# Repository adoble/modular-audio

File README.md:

# Modular Audio Project - Amplifier Module

An class D amplifier module that can select other digital sources (I2S, S/PDIF).

## System Diagram

### Functional Components

<!-- Removed the ELK renderer as causing problems - see https://github.com/mermaid-js/mermaid-cli/issues/594 -->
<!-- Old code was (first line of the mermaid description): -->
<!-- %%{init: {"flowchart": {"defaultRenderer": "elk"}} }%% -->

```mermaid
flowchart LR

main_ctrl["Main Controller"] -- Parallel Bus --- i2sm[I2S-Multiplexer];
wifi --- antenna1((Antenna <br> 1));

main_ctrl -- I2C --- dsp;
main_ctrl -- SPI+2 --- wifi["WiFi Co-Processor"]
i2sm -- I2S --- dsp["Digital Signal <br> Processor"] -- I2S --- amp[Amplifier];
dsp -- I2S --- toslink_out_converter[TOSLINK<br>Converter] -- "S/PDIF" --- toslink_out{{TOSLINK <br> Out}};

style dsp stroke-dasharray: 5 5;
style toslink_out_converter stroke-dasharray: 5 5;
style toslink_out stroke-dasharray: 5 5;

subgraph sources [Sources-In]
    cd{{CD}};
    dvd{{DVD}};
    tos_link_in{{Toslink In}}
end

subgraph source_sel_display [Source Selection Lights]
    direction LR
    cd_source_selected((CD ))
    dvd_source_selected((DVD))
    bluetooth_source_selected((BT ))
    wlan_source_selected((WLAN))
    dab_source_selected((DAB))
end

antenna2((Antenna <br> 2)) --- airlink;
airlink["Airlink/Bluetooth"] -- I2S --- i2sm
cd -- I2S  --- i2sm;
dvd -- "S/PDIF" --- spdif["S/PDIF Module"] -- I2S --- i2sm;
internet-radio["Internet Radio"] -- I2S --- i2sm

tos_link_in -- "S/PDIF" --- toslink_converter[TOSLINK<br>Converter] -- I2S --- i2sm; 
dab["DAB Radio"] -- I2S --- i2sm

amp --- left{{Left}} --- left_spk((Left <br> Speaker)) 
amp --- right{{Right}} --- right_spk((Right <br> Speaker)) 

dsp -- I2S --- sw-dac[Sub-Woofer DAC] --- sw-line-out{{Sub-Woofer<br>Line-Out}} --- active-sw((Active<br>Sub-Woofer))

vol_proc[Volume <br> Processor];
sel_source[Select <br> Source <br>];

subgraph controls[Controls]
    direction TB
    sel_source_btn((Select <br> Source Button))
    vol_knob((Volume <br> Knob))
end

sel_source --- source_sel_display
vol_knob --- vol_proc -- I2C+1--- main_ctrl;
sel_source_btn --- sel_source -- I2C+1--- main_ctrl;

%%click main_ctrl "https://github.com/adoble/modular-audio/blob/main/README.md#controller"%%
%%click i2sm "https://github.com/adoble/modular-audio/tree/main/hardware/i2s-multiplexer" "Click to see sub-repository"%%
```

### Power

```mermaid
    graph LR;

    net{{240V AV}};
    net ---- Relay;
    Relay --- smps[Switched Mode <br> Power Supply];
    smps ---- pwr_24v{24V};
    smps --- reg_5v[5V Regulator];
    smps --- reg_3v3[3.3V Regulator];
    reg_5v --- pwr_5v{5V};
    reg_3v3 --- pwr_3v3{3.3V};

    Battery --- pwr_on_off(("Power <br> On/Off <br> Switch")) --- Relay; 
```

### Symbols used in the Diagrams

```mermaid
graph LR;

subgraph key[Key]
    transducer((<small>Transducer<small>)) ---  pwr_net{<small>Power<br>Net<small>} --- module[<small>Hardware Module<small>] --- ext{{<small>External<br>Connection<small>}};
end
style key stroke-dasharray: 5 5, fill-opacity: 0;

%% Render links invisible
linkStyle 0 stroke:none
linkStyle 1 stroke:none
linkStyle 2 stroke:none
```

<!--  -->

## Functional Component Descriptions

### Controller

Work in Progress!

The controller has the following tasks:

* Select sources
* Receive input fron the volume control and adjust the volume over the DSP. 
* Receive input from the button banks. These are used to interact with the display. 
* Interface with an (Airlift) Wifi board over an extended SPI interface. This is used to download station lists and also 
to control the internet radio module.

Software is [here](/software/main-controller).

Hardware is [here](/hardware/controller).

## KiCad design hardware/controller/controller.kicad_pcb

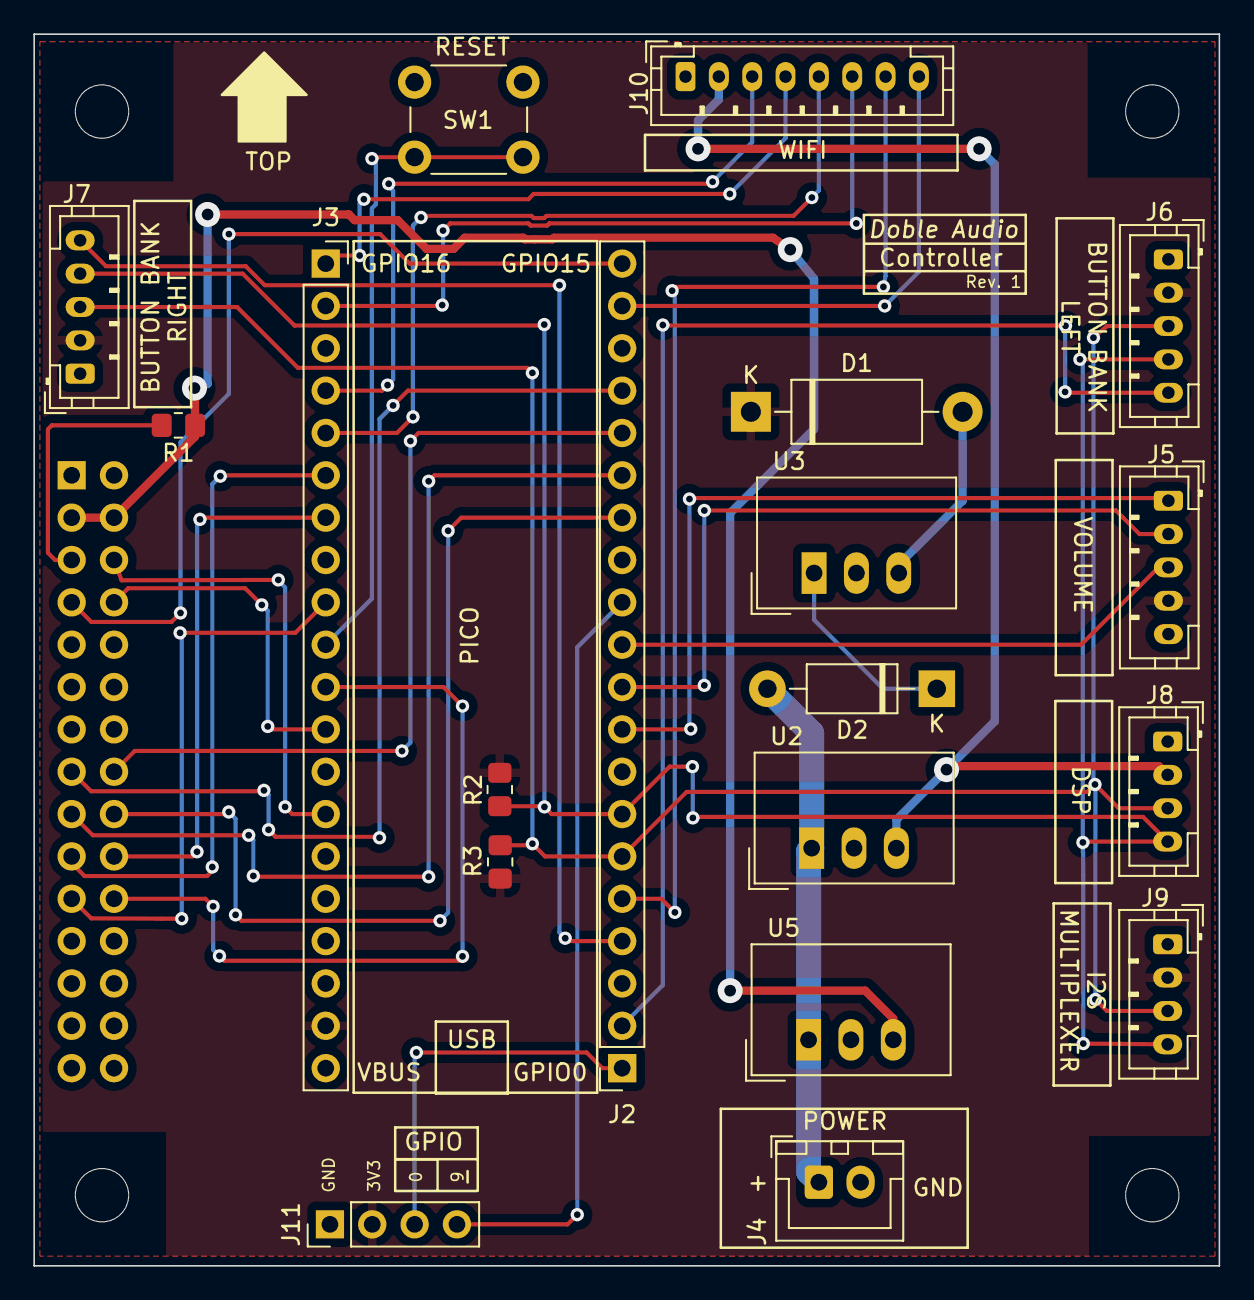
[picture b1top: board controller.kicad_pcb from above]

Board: 2 copper layers, 71.1 x 73.9 mm, 24 parts (1 on the bottom side), 35 nets.

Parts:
D1: D_Schottky; D_DO-15_P12.70mm_Horizontal
D2: 1N4007; D_DO-41_SOD81_P10.16mm_Horizontal
H1, H2, H3, H4: MountingHole; MountingHole_3.2mm_M3
J1: Conn_02x15_Odd_Even; PinSocket_2x15_P2.54mm_Vertical
J2, J3: Conn_01x20; PinSocket_1x20_P2.54mm_Vertical
J4: Conn_01x02; JST_XH_B2B-XH-A_1x02_P2.50mm_Vertical
J5: conn_vol; JST_PH_B5B-PH-K_1x05_P2.00mm_Vertical
J6: conn_bl; JST_PH_B5B-PH-K_1x05_P2.00mm_Vertical
J7: conn_br; JST_PH_B5B-PH-K_1x05_P2.00mm_Vertical
J8: conn_dsp; JST_PH_B4B-PH-K_1x04_P2.00mm_Vertical
J9: conn_i2s_mplx; JST_PH_B4B-PH-K_1x04_P2.00mm_Vertical
J10: conn_wifi; JST_PH_B8B-PH-K_1x08_P2.00mm_Vertical
J11: conn_gpio; PinHeader_1x04_P2.54mm_Vertical
R1: 10k; R_0805_2012Metric_Pad1.20x1.40mm_HandSolder
R2, R3: 2.2K; R_0805_2012Metric_Pad1.20x1.40mm_HandSolder
SW1: RESET; SW_PUSH_6mm_H4.3mm
U2, U3, U5: TSR_1-2433; Converter_DCDC_TRACO_TSR-1_THT

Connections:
+3V3: D1.1 (K), J3.19, J5.4, J6.2, J7.2, J9.2, J11.2, R2.1, R3.1
+3V3_AUX: J8.2, J10.2, U2.3 (Vout)
+3V3_DISPLAY: J1.3, J1.4, R1.1, U5.3 (Vout)
+24V: D2.2 (A), J4.1, U2.1 (Vin), U5.1 (Vin)
/DI.DATA0: J1.15, J2.17
/DI.DATA1: J1.16, J2.16
/DI.DATA2: J1.17, J2.15
/DI.DATA3: J1.18, J2.14
/DI.DATA4: J1.19, J3.6
/DI.DATA5: J1.20, J3.7
/DI.DATA6: J1.21, J3.9
/DI.DATA7: J1.22, J3.11
/DI.LCD_DCX: J1.8, J3.12
/DI.~LCD_WR: J1.6, J3.14
/GPIO0: J2.1, J11.3
/GPIO9: J2.12, J11.4
/I2C0_SCL: J2.7, J6.4, J7.4, J8.4, J9.4, R2.2
/I2C0_SDA: J2.6, J6.3, J7.3, J8.3, J9.3, R3.2
/INT_BL: J2.2, J6.5
/INT_BR: J2.4, J7.5
/LCD_READ: J1.5, R1.2
/MCU_RESET: J3.10, SW1.2
/SPI0_CS: J3.2, J10.6
/SPI0_RX: J3.1, J10.4
/SPI0_SCK: J3.4, J10.3
/SPI0_TX: J3.5, J10.5
/VOL_A: J2.9, J5.1
/VOL_B: J2.10, J5.2
/VOL_C: J2.11, J5.3
/WIFI_BUSY: J2.5, J10.7
/~LCD_CS: J1.7, J2.20
/~WIFI_RESET: J2.19, J10.8
GND: J1.1, J1.2, J1.13, J2.3, J2.8, J2.13, J2.18, J3.3, J3.8, J3.18, J4.2, J5.5, J6.1, J7.1, J8.1, J9.1, J10.1, J11.1, SW1.1, U2.2 (GND), U3.2 (GND), U5.2 (GND)
unnamed: D1.2 (A), U3.3 (Vout)
unnamed: D2.1 (K), U3.1 (Vin)

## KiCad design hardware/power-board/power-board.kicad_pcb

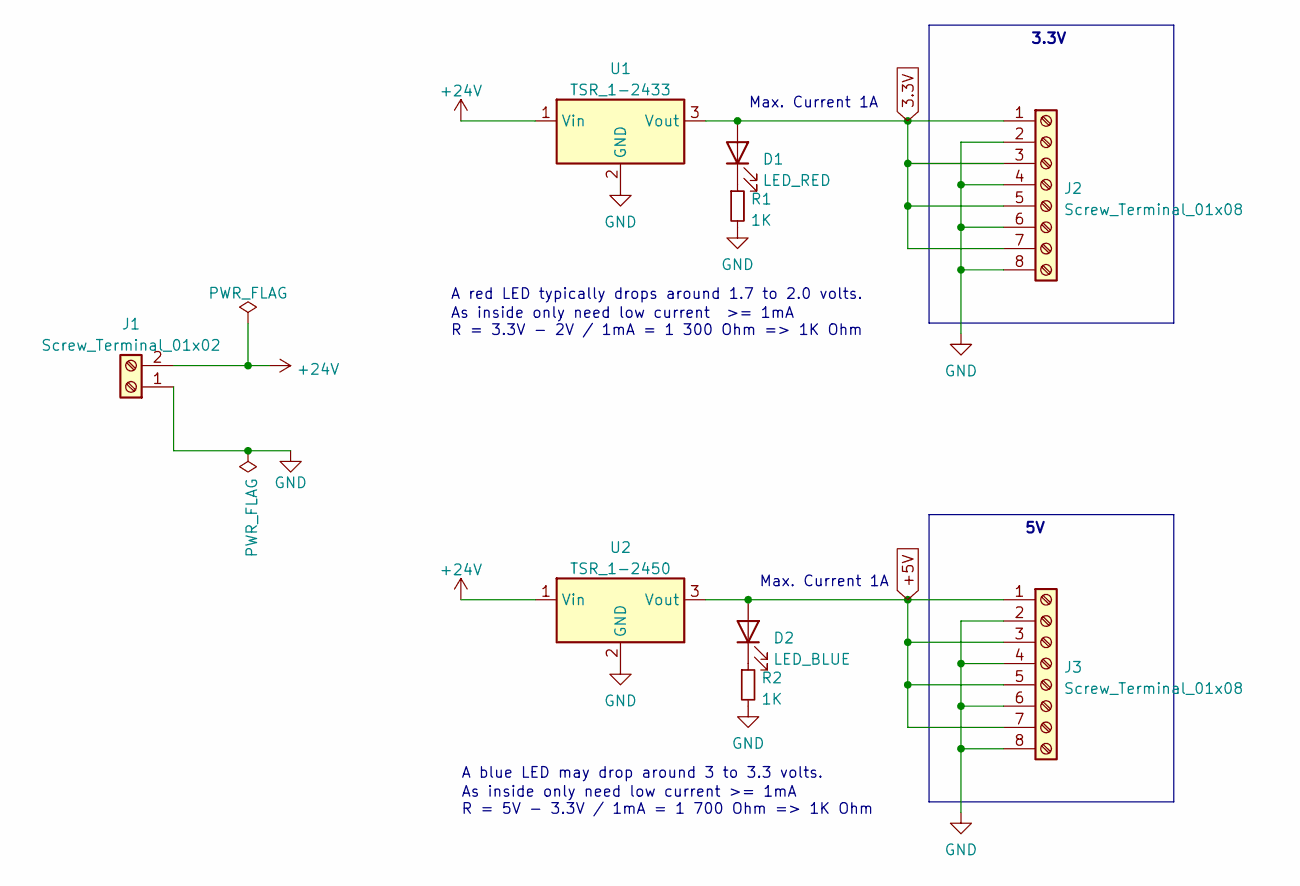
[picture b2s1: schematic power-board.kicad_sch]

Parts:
D1: LED_RED; LED_0805_2012Metric_Pad1.15x1.40mm_HandSolder
D2: LED_BLUE; LED_0805_2012Metric_Pad1.15x1.40mm_HandSolder
J1: Screw_Terminal_01x02; TerminalBlock_bornier-2_P5.08mm
J2, J3: Screw_Terminal_01x08; TerminalBlock_Phoenix_MKDS-3-8-5.08_1x08_P5.08mm_Horizontal
R1, R2: 1K; R_0805_2012Metric_Pad1.20x1.40mm_HandSolder
U1: TSR_1-2433; Converter_DCDC_TRACO_TSR-1_THT
U2: TSR_1-2450; Converter_DCDC_TRACO_TSR-1_THT

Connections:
3.3V: D1.2 (A), J2.1, J2.3, J2.5, J2.7, U1.3 (Vout)
+5V: D2.2 (A), J3.1, J3.3, J3.5, J3.7, U2.3 (Vout)
+24V: J1.2, U1.1 (Vin), U2.1 (Vin)
GND: J1.1, J2.2, J2.4, J2.6, J2.8, J3.2, J3.4, J3.6, J3.8, R1.2, R2.2, U1.2 (GND), U2.2 (GND)
unnamed: D1.1 (K), R1.1
unnamed: D2.1 (K), R2.1

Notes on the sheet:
Max. Current 1A
As inside only need low current >= 1mA R = 3.3V - 2V / 1mA = 1 300 Ohm => 1K Ohm
A red LED typically drops around 1.7 to 2.0 volts.
3.3V
As inside only need low current >= 1mA R = 5V - 3.3V / 1mA = 1 700 Ohm => 1K Ohm
A blue LED may drop around 3 to 3.3 volts.

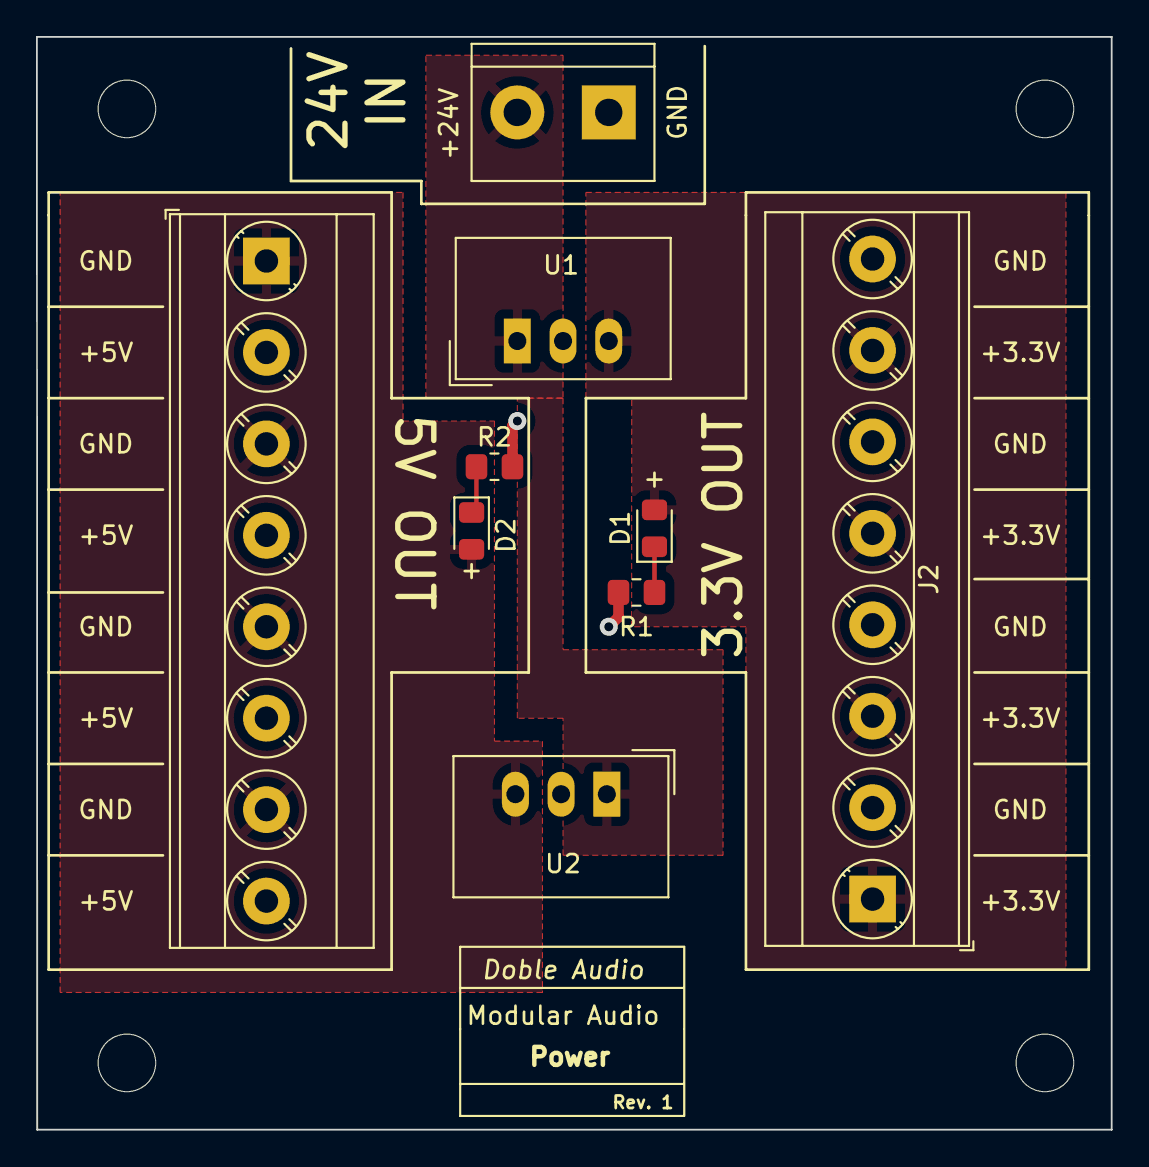
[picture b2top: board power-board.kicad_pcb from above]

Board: 2 copper layers, 59.7 x 60.7 mm, 9 parts (0 on the bottom side), 6 nets.

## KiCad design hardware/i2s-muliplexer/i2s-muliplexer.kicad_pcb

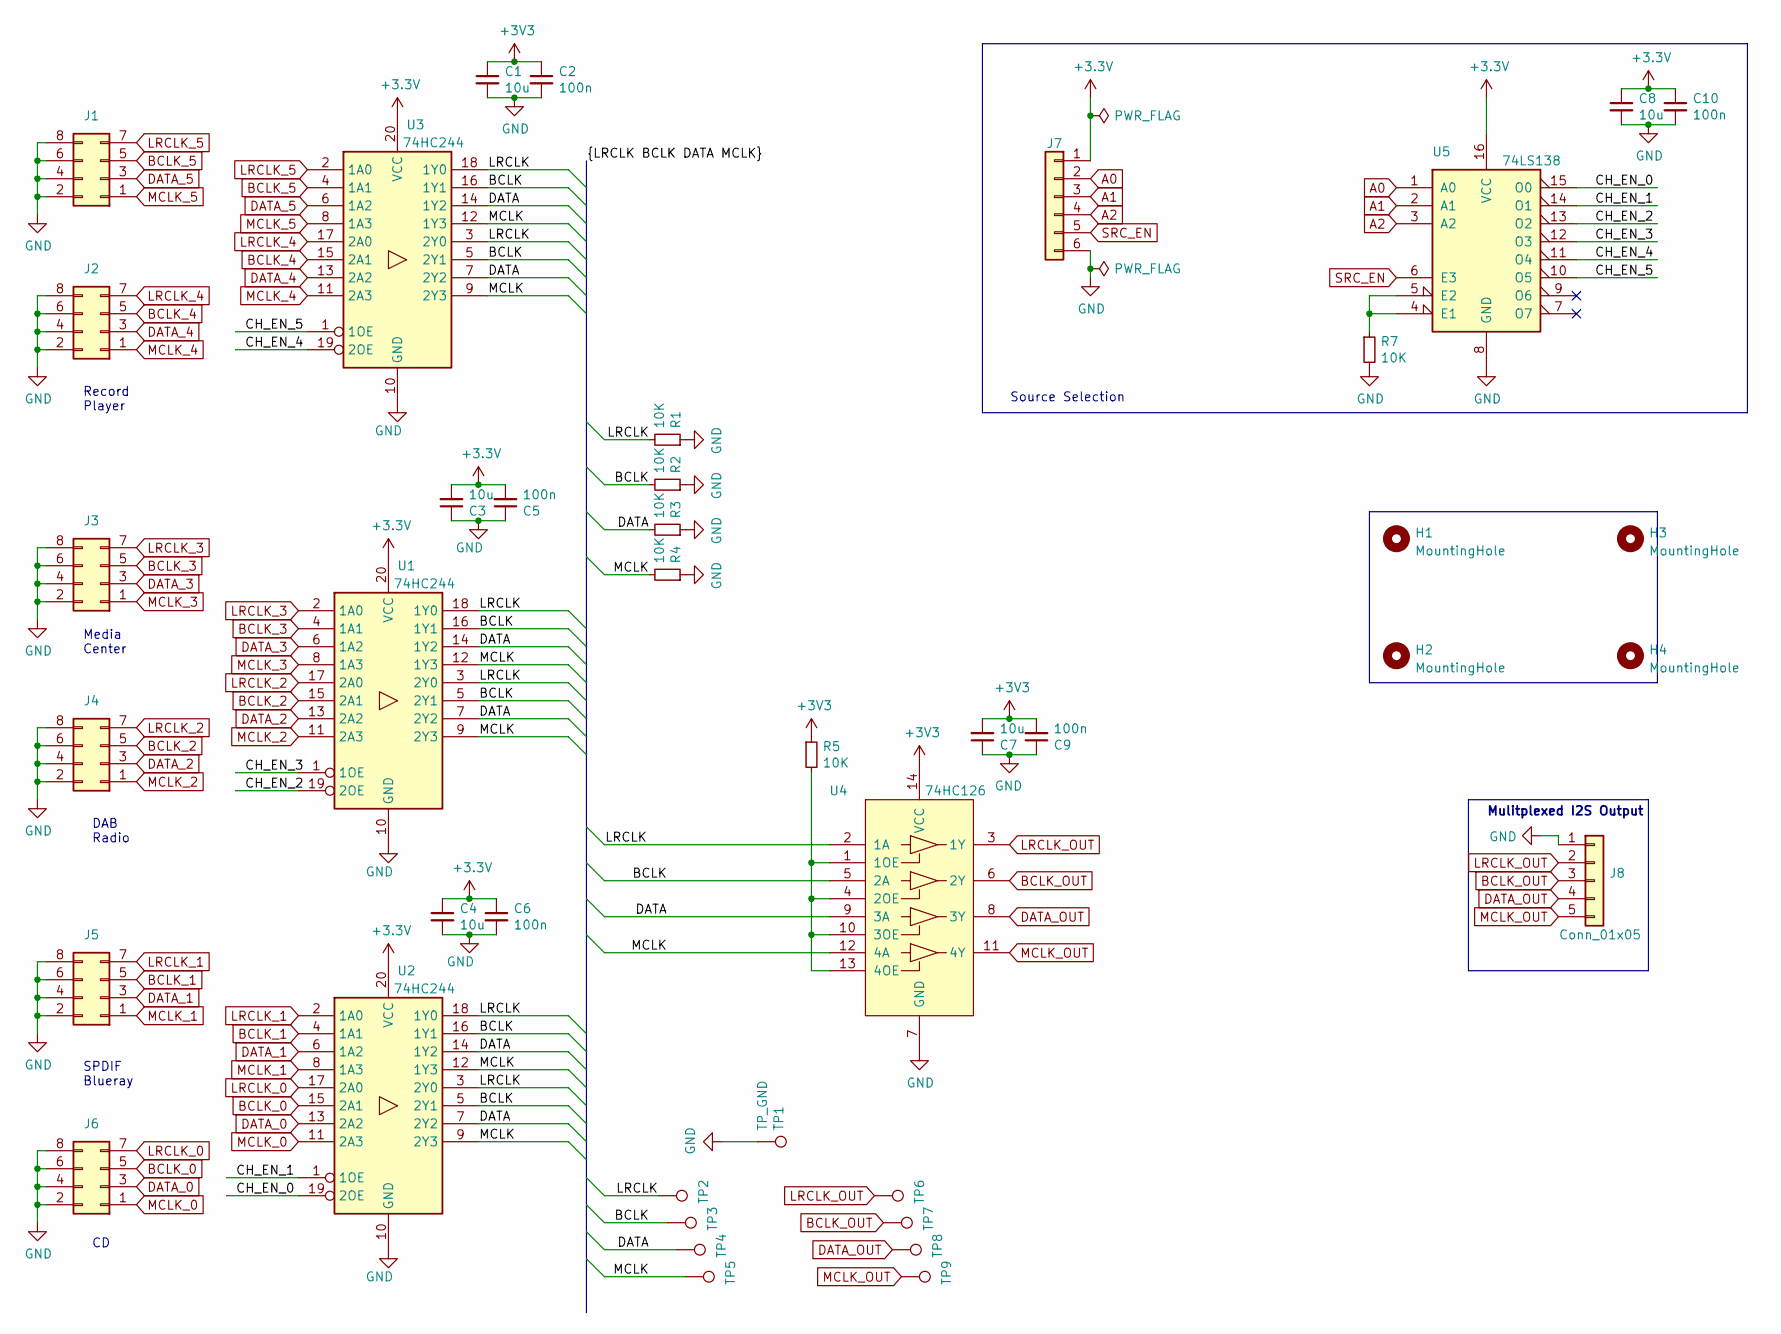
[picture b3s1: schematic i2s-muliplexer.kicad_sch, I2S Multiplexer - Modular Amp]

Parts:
C1, C3, C4, C7, C8: 10u; C_0805_2012Metric_Pad1.15x1.40mm_HandSolder
C2, C5, C6, C9, C10: 100n; C_0805_2012Metric_Pad1.15x1.40mm_HandSolder
H1, H2, H3, H4: MountingHole; MountingHole_3.2mm_M3_DIN965
J1, J2, J3, J4, J5, J6: Conn_02x04_Odd_Even; PinHeader_2x04_P2.54mm_Vertical
J7: Conn_01x06; PinHeader_1x06_P2.54mm_Vertical
J8: Conn_01x05; PinHeader_1x05_P2.54mm_Vertical
R1, R2, R3, R4, R5, R7: 10K; R_0805_2012Metric_Pad1.15x1.40mm_HandSolder
TP1: TP_GND; PinHeader_1x01_P2.54mm_Vertical
TP2, TP3, TP4, TP5, TP6, TP7, TP8, TP9: TestPoint; TestPoint_Pad_2.0x2.0mm
U1, U2, U3: 74HC244; SOIC-20W_7.5x12.8mm_P1.27mm
U4: 74HC126; SOIC-14_3.9x8.7mm_P1.27mm
U5: 74LS138; SOIC-16_3.9x9.9mm_P1.27mm

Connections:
/BCLK: R2.2, TP3.1, U1.5 (2Y1), U1.16 (1Y1), U2.5 (2Y1), U2.16 (1Y1), U3.5 (2Y1), U3.16 (1Y1), U4.5 (2A)
/CH_EN_0: U2.19 (2OE), U5.15 (O0)
/CH_EN_1: U2.1 (1OE), U5.14 (O1)
/CH_EN_2: U1.19 (2OE), U5.13 (O2)
/CH_EN_3: U1.1 (1OE), U5.12 (O3)
/CH_EN_4: U3.19 (2OE), U5.11 (O4)
/CH_EN_5: U3.1 (1OE), U5.10 (O5)
/DATA: R3.2, TP4.1, U1.7 (2Y2), U1.14 (1Y2), U2.7 (2Y2), U2.14 (1Y2), U3.7 (2Y2), U3.14 (1Y2), U4.9 (3A)
/LRCLK: R1.2, TP2.1, U1.3 (2Y0), U1.18 (1Y0), U2.3 (2Y0), U2.18 (1Y0), U3.3 (2Y0), U3.18 (1Y0), U4.2 (1A)
/MCLK: R4.2, TP5.1, U1.9 (2Y3), U1.12 (1Y3), U2.9 (2Y3), U2.12 (1Y3), U3.9 (2Y3), U3.12 (1Y3), U4.12 (4A)
A0: J7.2, U5.1 (A0)
A1: J7.3, U5.2 (A1)
A2: J7.4, U5.3 (A2)
BCLK_0: J6.5, U2.15 (2A1)
BCLK_1: J5.5, U2.4 (1A1)
BCLK_2: J4.5, U1.15 (2A1)
BCLK_3: J3.5, U1.4 (1A1)
BCLK_4: J2.5, U3.15 (2A1)
BCLK_5: J1.5, U3.4 (1A1)
BCLK_OUT: J8.3, TP7.1, U4.6 (2Y)
DATA_0: J6.3, U2.13 (2A2)
DATA_1: J5.3, U2.6 (1A2)
DATA_2: J4.3, U1.13 (2A2)
DATA_3: J3.3, U1.6 (1A2)
DATA_4: J2.3, U3.13 (2A2)
DATA_5: J1.3, U3.6 (1A2)
DATA_OUT: J8.4, TP8.1, U4.8 (3Y)
GND: C1.2, C2.2, C3.1, C4.2, C5.1, C6.2, C7.1, C8.2, C9.1, C10.2, J1.2, J1.4, J1.6, J1.8, J2.2, J2.4, J2.6, J2.8, J3.2, J3.4, J3.6, J3.8, J4.2, J4.4, J4.6, J4.8, J5.2, J5.4, J5.6, J5.8, J6.2, J6.4, J6.6, J6.8, J7.6, J8.1, R1.1, R2.1, R3.1, R4.1, R7.2, TP1.1, U1.10 (GND), U2.10 (GND), U3.10 (GND), U4.7 (GND), U5.8 (GND); also elsewhere on the board
LRCLK_0: J6.7, U2.17 (2A0)
LRCLK_1: J5.7, U2.2 (1A0)
LRCLK_2: J4.7, U1.17 (2A0)
LRCLK_3: J3.7, U1.2 (1A0)
LRCLK_4: J2.7, U3.17 (2A0)
LRCLK_5: J1.7, U3.2 (1A0)
LRCLK_OUT: J8.2, TP6.1, U4.3 (1Y)
MCLK_0: J6.1, U2.11 (2A3)
MCLK_1: J5.1, U2.8 (1A3)
MCLK_2: J4.1, U1.11 (2A3)
MCLK_3: J3.1, U1.8 (1A3)
MCLK_4: J2.1, U3.11 (2A3)
MCLK_5: J1.1, U3.8 (1A3)
MCLK_OUT: J8.5, TP9.1, U4.11 (4Y)
unnamed: R5.2, U4.1 (1OE), U4.4 (2OE), U4.10 (3OE), U4.13 (4OE)
unnamed: R7.1, U5.4 (E1), U5.5 (E2)
SRC_EN: J7.5, U5.6 (E3)

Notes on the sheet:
Mulitplexed I2S Output
Media Center
Source Selection
SPDIF Blueray
Record Player
DAB Radio

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
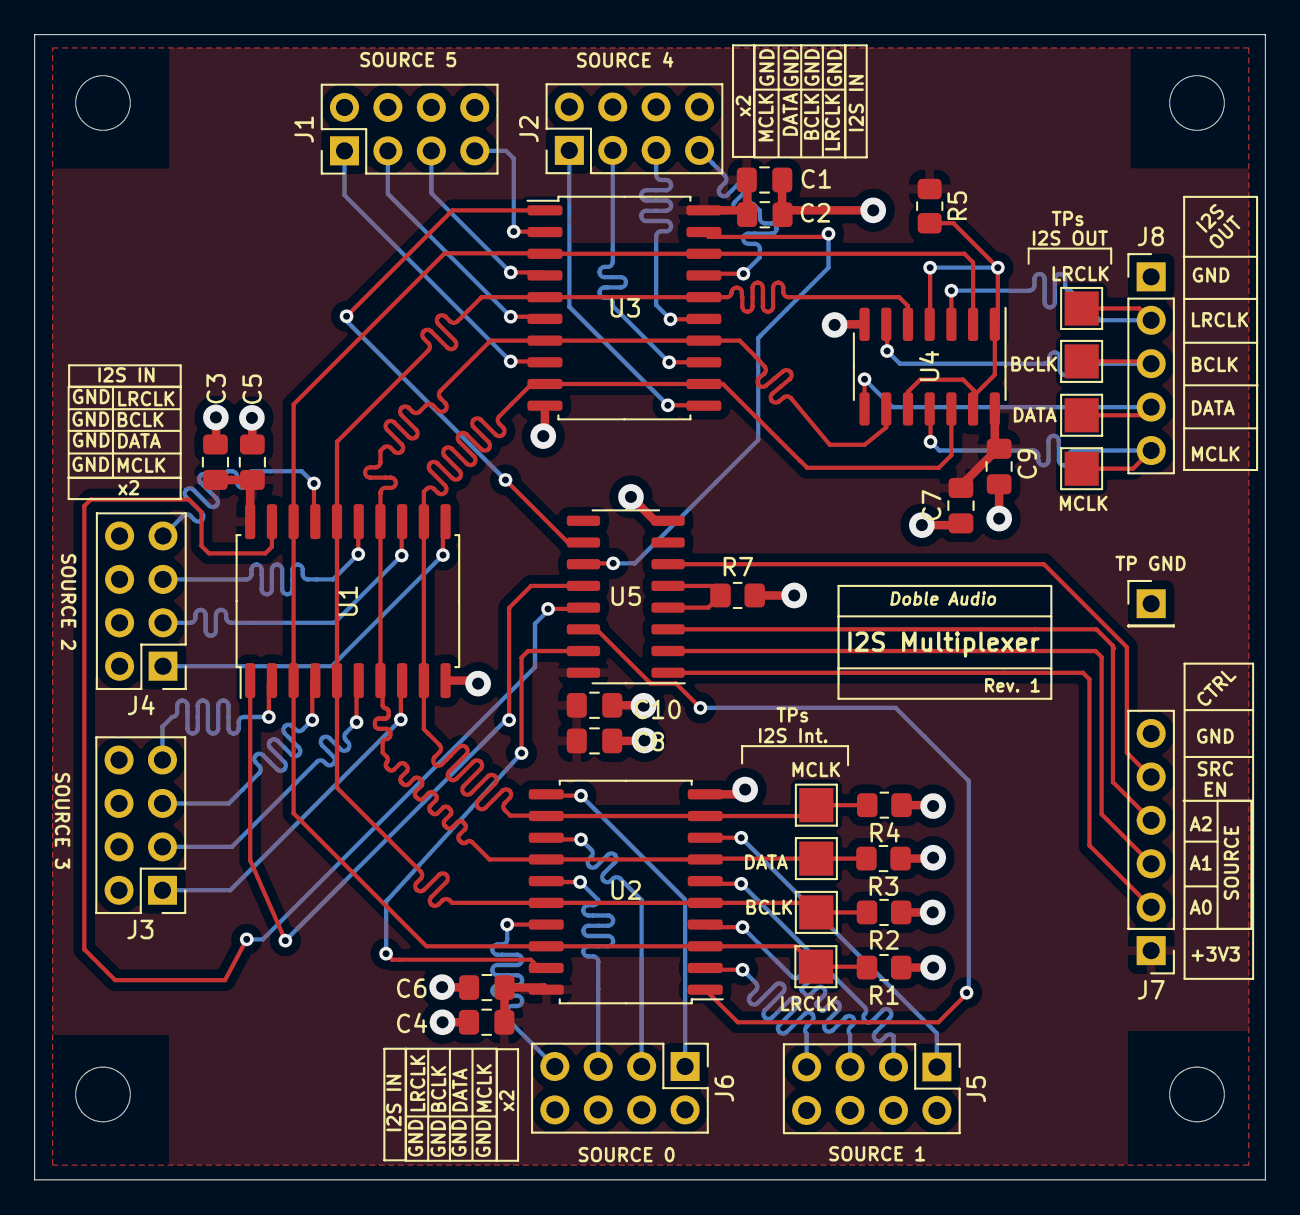
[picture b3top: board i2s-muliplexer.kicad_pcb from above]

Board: 2 copper layers, 72.0 x 67.0 mm, 42 parts (0 on the bottom side), 46 nets.

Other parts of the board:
TP GND: TP_GND; PinHeader_1x01_P2.54mm_Vertical

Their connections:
GND: TP GND.1; also elsewhere on the board

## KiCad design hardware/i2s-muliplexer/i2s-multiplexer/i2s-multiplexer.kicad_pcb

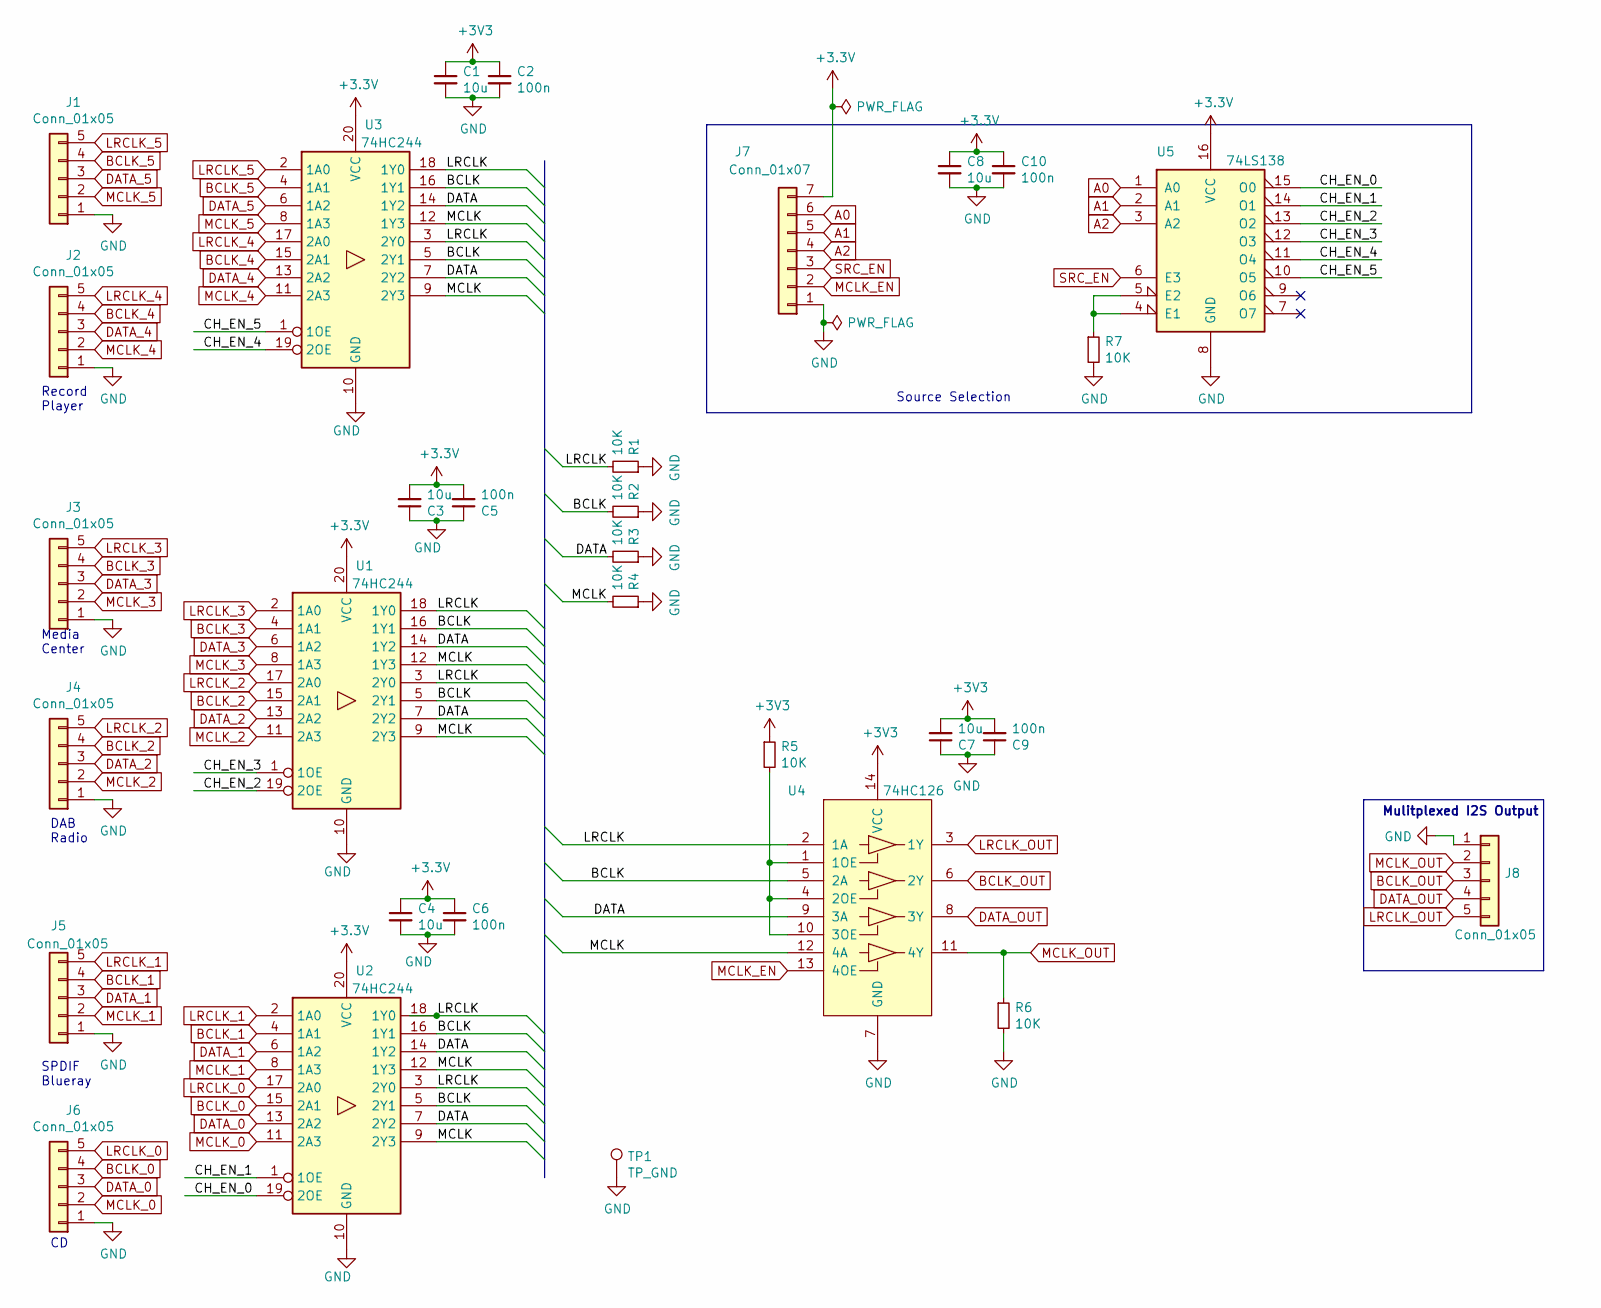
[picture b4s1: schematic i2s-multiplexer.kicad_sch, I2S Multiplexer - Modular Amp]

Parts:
C1, C3, C4, C7, C8: 10u; C_0805_2012Metric_Pad1.15x1.40mm_HandSolder
C2, C5, C6, C9, C10: 100n; C_0805_2012Metric_Pad1.15x1.40mm_HandSolder
J1, J2, J3, J4, J5, J6, J8: Conn_01x05; PinHeader_1x05_P2.54mm_Vertical
J7: Conn_01x07; PinHeader_1x07_P2.54mm_Vertical
R1, R2, R3, R4, R5, R6, R7: 10K; R_0805_2012Metric_Pad1.15x1.40mm_HandSolder
TP1: TP_GND; PinHeader_1x01_P2.54mm_Vertical
U1, U2, U3: 74HC244; SOIC-20W_7.5x12.8mm_P1.27mm
U4: 74HC126; SOIC-14_3.9x8.7mm_P1.27mm
U5: 74LS138; SOIC-16_3.9x9.9mm_P1.27mm

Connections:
/BCLK: R2.2, U1.5 (2Y1), U1.16 (1Y1), U2.5 (2Y1), U2.16 (1Y1), U3.5 (2Y1), U3.16 (1Y1), U4.5 (2A)
/CH_EN_0: U2.19 (2OE), U5.15 (O0)
/CH_EN_1: U2.1 (1OE), U5.14 (O1)
/CH_EN_2: U1.19 (2OE), U5.13 (O2)
/CH_EN_3: U1.1 (1OE), U5.12 (O3)
/CH_EN_4: U3.19 (2OE), U5.11 (O4)
/CH_EN_5: U3.1 (1OE), U5.10 (O5)
/DATA: R3.2, U1.7 (2Y2), U1.14 (1Y2), U2.7 (2Y2), U2.14 (1Y2), U3.7 (2Y2), U3.14 (1Y2), U4.9 (3A)
/LRCLK: R1.2, U1.3 (2Y0), U1.18 (1Y0), U2.3 (2Y0), U2.18 (1Y0), U3.3 (2Y0), U3.18 (1Y0), U4.2 (1A)
/MCLK: R4.2, U1.9 (2Y3), U1.12 (1Y3), U2.9 (2Y3), U2.12 (1Y3), U3.9 (2Y3), U3.12 (1Y3), U4.12 (4A)
A0: J7.6, U5.1 (A0)
A1: J7.5, U5.2 (A1)
A2: J7.4, U5.3 (A2)
BCLK_0: J6.4, U2.15 (2A1)
BCLK_1: J5.4, U2.4 (1A1)
BCLK_2: J4.4, U1.15 (2A1)
BCLK_3: J3.4, U1.4 (1A1)
BCLK_4: J2.4, U3.15 (2A1)
BCLK_5: J1.4, U3.4 (1A1)
BCLK_OUT: J8.3, U4.6 (2Y)
DATA_0: J6.3, U2.13 (2A2)
DATA_1: J5.3, U2.6 (1A2)
DATA_2: J4.3, U1.13 (2A2)
DATA_3: J3.3, U1.6 (1A2)
DATA_4: J2.3, U3.13 (2A2)
DATA_5: J1.3, U3.6 (1A2)
DATA_OUT: J8.4, U4.8 (3Y)
GND: C1.2, C2.2, C3.1, C4.2, C5.1, C6.2, C7.1, C8.2, C9.1, C10.2, J1.1, J2.1, J3.1, J4.1, J5.1, J6.1, J7.1, J8.1, R1.1, R2.1, R3.1, R4.1, R6.2, R7.2, TP1.1, U1.10 (GND), U2.10 (GND), U3.10 (GND), U4.7 (GND), U5.8 (GND)
LRCLK_0: J6.5, U2.17 (2A0)
LRCLK_1: J5.5, U2.2 (1A0)
LRCLK_2: J4.5, U1.17 (2A0)
LRCLK_3: J3.5, U1.2 (1A0)
LRCLK_4: J2.5, U3.17 (2A0)
LRCLK_5: J1.5, U3.2 (1A0)
LRCLK_OUT: J8.5, U4.3 (1Y)
MCLK_0: J6.2, U2.11 (2A3)
MCLK_1: J5.2, U2.8 (1A3)
MCLK_2: J4.2, U1.11 (2A3)
MCLK_3: J3.2, U1.8 (1A3)
MCLK_4: J2.2, U3.11 (2A3)
MCLK_5: J1.2, U3.8 (1A3)
MCLK_EN: J7.2, U4.13 (4OE)
MCLK_OUT: J8.2, R6.1, U4.11 (4Y)
unnamed: R5.2, U4.1 (1OE), U4.4 (2OE), U4.10 (3OE)
unnamed: R7.1, U5.4 (E1), U5.5 (E2)
SRC_EN: J7.3, U5.6 (E3)

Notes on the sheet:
Mulitplexed I2S Output
Media Center
Source Selection
SPDIF Blueray
Record Player
DAB Radio

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
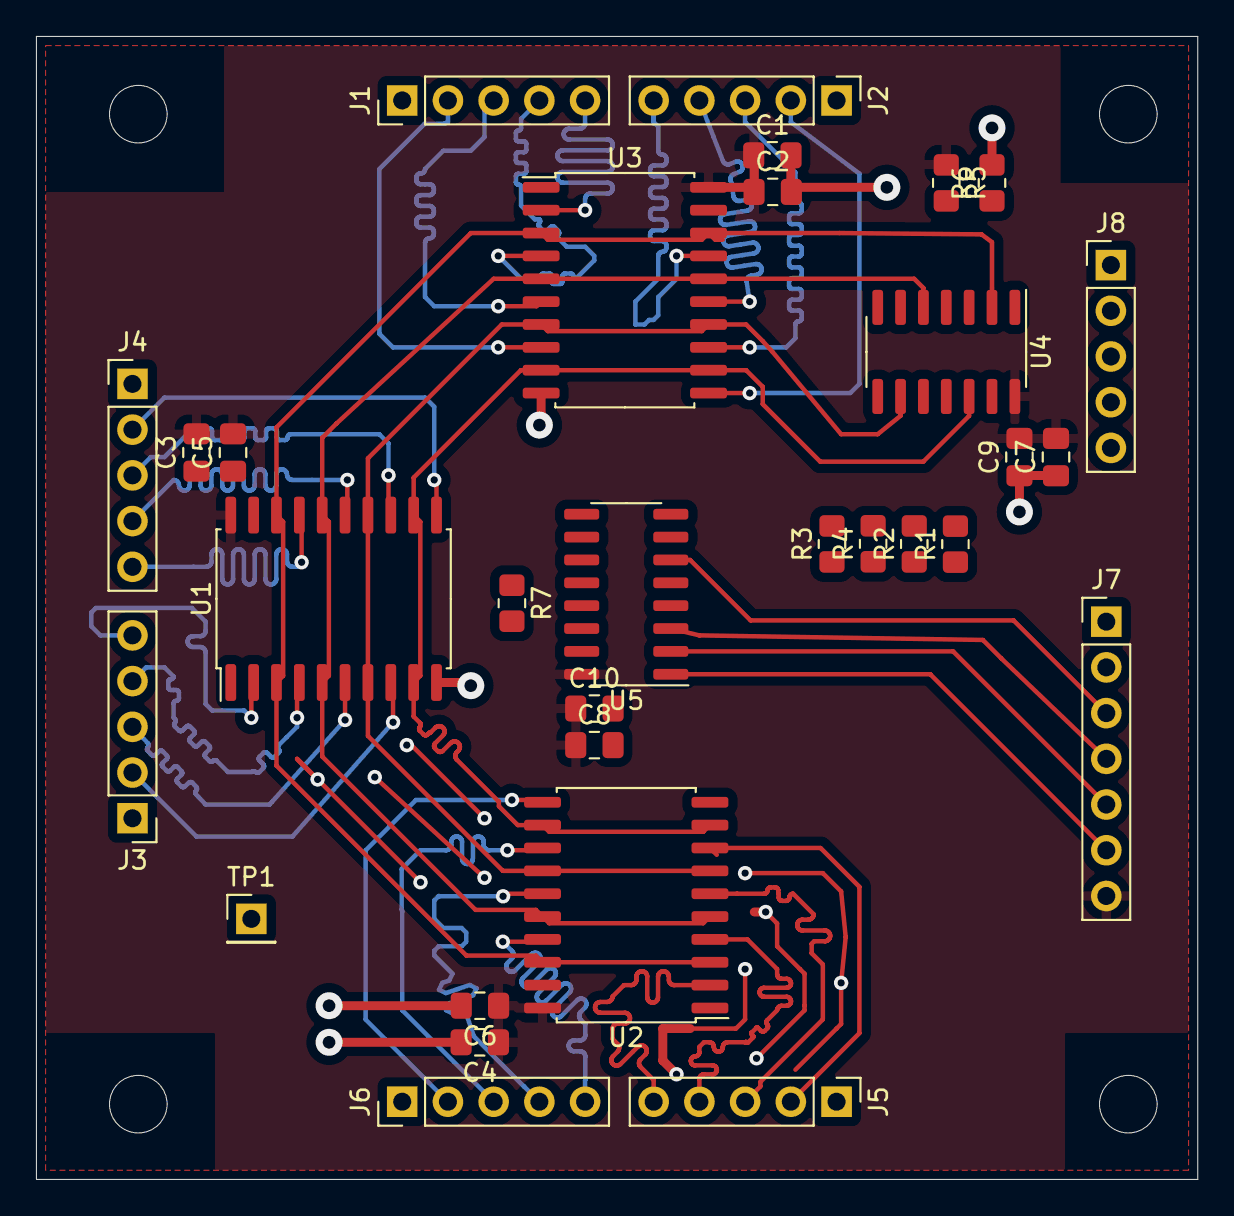
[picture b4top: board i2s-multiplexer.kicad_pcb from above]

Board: 2 copper layers, 64.5 x 63.5 mm, 31 parts (0 on the bottom side), 47 nets.

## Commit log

2021-01-26 I2C connection to TAS5754 code compiles
2022-01-17 Version with 4051 multiplexers as routers
2022-01-17 Using buffers
2022-01-26 Initial PCB design
2022-01-26 Added test point
2022-01-27 Moved component together
2022-01-27 Tuned i2s input tracks
2022-01-27 Rationalised bus structure
2022-02-01 Minor routing changes
2022-02-01 Removed i2s-tone-gen
2022-02-02 Initial placement
2022-02-07 Input trace track length tuning
2022-02-15 Updated to KiCad 6
2022-02-17 Test circuit can route i2s signals
2022-02-18 Added i2s multiplexer test code
2022-02-18 Added .gitignore
2022-02-18 Rationalised directory structure
2022-02-20 Layout with double row connectors
2022-02-20 Added symbols and adjusted silkscreen
2022-02-20 Corrected mounting hole positions
2022-02-20 Changed solder mask margins to 0 (default)
2022-02-23 Initial ayout power board
2022-03-03 Created use case model
2022-03-09 Correct spelling directory name
2022-03-10 Smaller board
2022-03-10 Updated explanatory notes on schematic
2022-03-11 More use cases
2022-03-19 Removed tone generator code
2022-03-21 Changed readme diagram to light mode
2022-03-21 Added updated system diagram using mermaid
2022-03-21 Added TOSLINK components
2022-03-22 Updated diagrams in README
2022-03-24 Initial code
2022-03-24 Updated .gitignore
2022-03-24 Extended UI
2022-03-24 Added DAB module
2022-03-24 Added more icons
2022-03-24 Adjusted width of select buttons
2022-03-25 Added WiFI Co-Processor component
2022-03-25 Select source text size increased
2022-03-25 Change text colour
2022-03-25 Restructured the slint files
2022-03-26 Added new screens - but not linked yet
2022-03-26 build script now looks in complete ui directory
2022-03-26 Restuctured color codes
2022-03-26 Gradient correct when SelectButton reversed-order property is true
2022-03-26 Basic screen traversal logic implmented
2022-03-28 Select buttons have a radio button function
2022-03-30 Start of bluetooth screen and screen transition effects
2022-03-30 Update i2s-multiplexer docs
2022-03-30 Added Pre-Amp
2022-03-30 Updated main-controller README
2022-04-01 Added screen ids
2022-04-01 Integrated bluetooth screen
2022-04-01 Extended bluetooth screen with image
2022-04-02 Settings use cases
2022-04-02 Extended to 7 inch screen
2022-04-02 Added settings use cases
2022-04-04 Restructured use case diagrams
2022-04-04 Source channel defaults to 2
2022-04-05 Select buttons now flash
2022-04-11 Skeleton of callbacks to rust program
2022-04-11 Refactored source and select button ids
2022-04-12 More work on callbacks
2022-04-20 Demo of timer (as BT connect simulation) works
2022-04-20 Icons indicate bluetooth connect status
2022-04-20 Refactored the bluetooth screen (too many elements)
2022-04-20 Added addtional text for bluetooth connect status
2022-04-21 Tidied up Ãcallback terminal messages
2022-08-16 Initial I2S output with PIO - generates sine wave
2022-08-16 Changed package name
2022-08-16 Changed to 5 inch display
2022-08-16 Attempt at documenting the traits used
2022-08-16 Schematic with 3.5 inch display and Pico board
2022-08-19 Got clock div right - Can hear a tone
2022-08-20 Refactoring clock divisor calculation and volume
2022-08-29 Changed the pins
2022-08-30 Frequency formular
2022-09-01 Sub-Woofer
2022-10-16 Diagram (mermaid) interaction> experiment
2022-10-16 Diagram (mermaid) interaction experiment
2022-11-04 Pinout for the RA8895 based 5 inch display
2022-12-03 Removed 3.5 inch display from schematic
2022-12-03 Revised powerchain (diode, new symbol)
2022-12-07 Added sense signal
2023-01-29 Added 8080 bus
2023-02-11 Updated interfaces
2023-02-15 Controller schematic and PCB design
2023-02-15 Added brief controller description
2023-02-15 Update links
2023-02-17 Update diagram
2023-02-22 Initial sketch of the select-button-board
2023-02-22 Initial schematic of select-button-board
2023-02-23 Simplified directory structure
2023-03-04 Added (temp) backlight control
2023-03-08 Corrections as of now
2023-03-21 Updated and new pictures of circuts/boards etc.
2023-03-21 New schematic for the system wiring
2023-03-21 KiCad version changes
2023-03-21 Corrections to schematics. WARNING PCB out of date
2023-03-21 Notification that branch has been abandoned.
2023-03-21 New means of source selection
2023-03-21 Rearranging the system diagram
2023-03-23 New KiCad version
2023-03-23 Initial design of source display processor
2023-03-30 Updated system diagram
2023-04-01 Added sequence diagram for controller
2023-04-03 changed_source
2023-04-03 Changed name of the interrupt to SOURCE_CHANGED
2023-04-04 Complete revamp that uses RTIC and no display
2023-04-04 Skeleton of i2s-multiplexer
2023-04-04 Correction
2023-04-05 Added new components
2023-04-06 Added functions to i2c-multiplexer
2023-04-06 Added corrections regarding the i2s-multiplexer interface
2023-04-06 Removed experimental termination as it is not required
2023-04-11 Added the I2SMultiplexer driver lib
2023-04-11 Updated embedded-hal to 0.2.7
2023-04-11 source-select-driver is now a module
2023-04-12 Extracted Source into seperate file
2023-04-12 Added source_channel_map
2023-04-12 Initial use of external crate enum_map
2023-04-14 Source converted from enum to struct
2023-04-16 Using references to sources in all_sources
2023-04-16 Got rid of lifetimes
2023-04-18 More formalism
2023-04-18 So close - yet so far away!
2023-04-22 Current state before trying a new source structure
2023-04-22 Integrated new source structure
2023-04-22 Removed sources in Shared. Compiles now
2023-04-22 Corrected warnings
2023-04-22 Removed some commented out code
2023-04-23 Updated dependencies diagram
2023-05-04 Current unfinished state
2023-05-07 Cleaning up loose ends
2023-05-07 Compiles!
2023-05-08 Added activate_initial_source task - does not now crash
2023-05-08 Removed redundant code
2023-05-08 Iterator functions correctly
2023-05-08 Added annotation
2023-05-08 Addresses i2s-multiplexer correctly
2023-05-08 Updated diagram
2023-05-08 KIcad changed this
2023-05-21 Added new tasks
2023-07-02 Small changes to controller circuit
2023-07-02 Removed aux, added internet-radio
2023-09-13 Explicit version of defmt - reqd for picoprobe
2023-09-13 Keep up to date with actual circuit
2023-09-13 Feature is stable since 1.68.0
2023-09-15 Added issue
2023-10-01 DOES NOT COMPILE - needs work on Sources
2023-10-02 DOES NOT COMPILE - Added test config attribute
2023-10-12 Moved channel and sources to lib
2023-10-14 Compiles - with known errors - but test does not work
2023-10-14 Nested workspaces - Compiles and tests work
2023-10-14 New structure compiles and tests work
2023-10-15 Removed SourceIterator
2023-10-16 Added tests for Channel
2023-10-16 Noted that simpler NOT to use interrupt pins
2023-10-16 Embassy refactor completed - working version
2023-10-16 Removed - a lot of! - old comments
2023-10-16 Removed warnings
2023-10-16 Clippy
2023-10-16 Modified README
2023-10-16 Removed old files
2023-10-17 Updated TODOs
2023-10-17 CHANGE_SOURCE directly driven from push button
2023-10-17 Removed MCP23017 interrupt configuration code
2023-10-17 Removed the troublesome ELK renderer
2023-10-19 Corrected interrupt bug
2023-10-19 Updated docs
2023-10-19 activate() fuction
2023-10-19 First specific activation functions
2023-10-19 Added aux channel
2023-10-20 Added candidate logos
2023-10-20 Added idea to doc
2023-10-20 Can coordinate multiple devices
2023-10-21 GPIO currently used for UART1 documented
2023-11-07 Added no connection symbol
2023-11-07 Added RC reset circuit
